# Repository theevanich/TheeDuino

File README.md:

# TheeDuino
My own Arduino board with a RTC!

To open the project with Kicad open atmega328p.pro with Kicad
For schematics see atmega328p.sch
For the PCB see atmega328p.kicad_pcb
Arduino Uno R3 board layout see Arduino_As_Uno.kicad_pcb

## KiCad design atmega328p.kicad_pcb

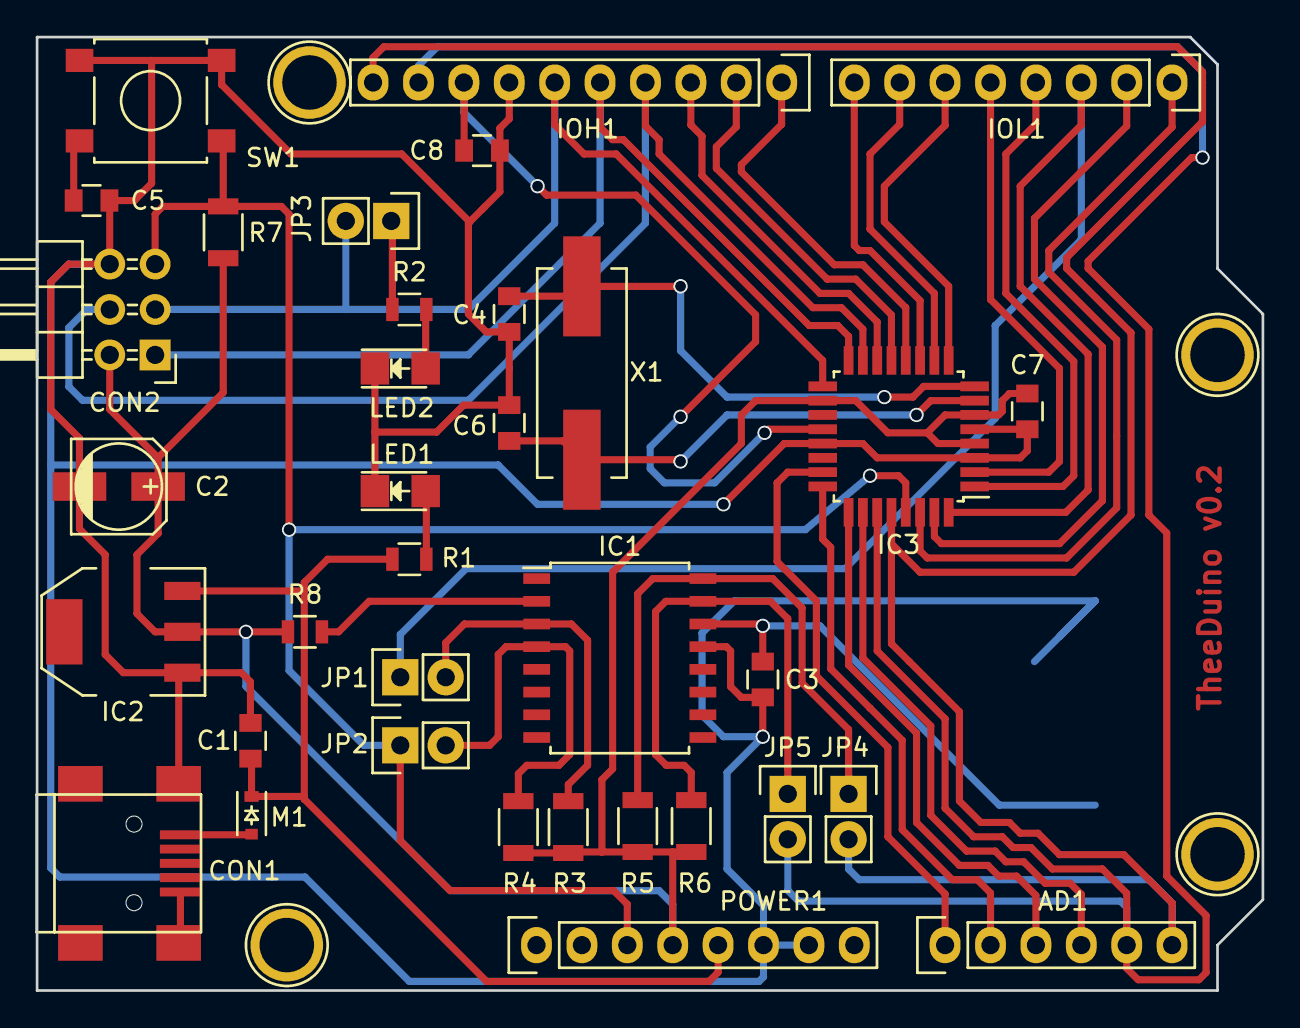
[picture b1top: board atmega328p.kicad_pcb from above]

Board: 2 copper layers, 68.6 x 53.3 mm, 40 parts (1 on the bottom side), 37 nets.

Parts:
AD1: PORT C; Socket_Strip_Arduino_1x06
BATT1: CR2032; 20mmBattHolder
C1, C3, C5, C7, C8: 100nF; C_0805
C2: 10uF; c_elec_5x5.8
C4, C6: 27p; C_0805
CON1: Micro USB; USB_Mini-B
CON2: AVR-ISP-6; Pin_Header_Angled_2x03
IC1: DS3231M_SO16; SOIC-16W_7.5x10.3mm_Pitch1.27mm
IC2: LD1117; SOT-223
IC3: ATMEGA328P-TQFP32; TQFP-32_7x7mm_Pitch0.8mm
IOH1: CONN_01X10; Socket_Strip_Arduino_1x10
IOL1: PORT D; Socket_Strip_Arduino_1x08
JP1, JP2, JP3, JP4, JP5: 1; Pin_Header_Straight_1x02
LED1: POWER; LED_1206
LED2: L; LED_1206
M1: D1; SOD-323
P5, P6, P7, P8: CONN_1; Arduino_1pin
POWER1: POWER; Socket_Strip_Arduino_1x08
R1: 500R; R_0805
R2: 330R; R_0805
R3, R4, R5, R6, R7: 10K; R_1206
R8: 0; R_0805
SW1: RESET; SW_SPST_B3S-1000
X1: 16 MHz; Crystal_HC49-SD_SMD

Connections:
+3V3: C2.1, C7.1, CON2.2, IC2.2, IC3.4, IC3.6, IC3.18, POWER1.4, R3.1, R4.1, R5.2, R6.2, R7.1, R8.1
+5V: C1.1, IC2.3, M1.1, POWER1.5, R1.1
AREF: C8.1, IC3.20, IOH1.8
GND: BATT1.1, C1.2, C2.2, C3.2, C4.2, C5.2, C6.2, C7.2, C8.2, CON1.5, CON1.6, CON2.6, IC1.13, IC2.1, IC3.3, IC3.5, IC3.21, IOH1.7, LED1.1, LED2.1, POWER1.6, POWER1.7, SW1.1
INT0: IC3.32, IOL1.3, JP1.1
unnamed: AD1.1, IC3.23
unnamed: AD1.2, IC3.24
unnamed: AD1.3, IC3.25
unnamed: AD1.4, IC3.26
unnamed: BATT1.2, BATT1.3, C3.1, IC1.14
unnamed: C4.1, IC3.8, X1.1
unnamed: C6.1, IC3.7, X1.2
unnamed: CON1.1, M1.2
unnamed: CON2.1, IC3.16, IOH1.5
unnamed: CON2.4, IC3.15, IOH1.4
unnamed: IC1.2, R8.2
unnamed: IC1.3, JP1.2, R3.2
unnamed: IC1.4, JP2.2, R4.2
unnamed: IC1.15, JP5.1, R6.1
unnamed: IC1.16, JP4.1, R5.1
unnamed: IC3.1, IOL1.4
unnamed: IC3.2, IOL1.5
unnamed: IC3.9, IOL1.6
unnamed: IC3.10, IOL1.7
unnamed: IC3.11, IOL1.8
unnamed: IC3.12, IOH1.1
unnamed: IC3.13, IOH1.2
unnamed: IC3.14, IOH1.3
unnamed: IC3.30, IOL1.1
unnamed: IC3.31, IOL1.2
unnamed: JP3.1, R2.1
unnamed: LED1.2, R1.2
unnamed: LED2.2, R2.2
PB5: CON2.3, IC3.17, IOH1.6, JP3.2
RST: C5.1, CON2.5, IC3.29, JP2.1, POWER1.3, R7.2, SW1.2
SCL: AD1.6, IC3.28, IOH1.10, JP4.2
SDA: AD1.5, IC3.27, IOH1.9, JP5.2

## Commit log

2016-08-15 :circus_tent: Added .gitattributes
2016-08-15 [Add] .gitignore
    to filter out unwanted files in the projects
2016-08-15 Create Readme.md
    Please read me!
2016-08-15 this is needed to be able to see atmega328p in sch
2016-08-15 Update .gitignore
    removed *cache* as it is needed to see some components
2016-08-15 added gerbers and some minor changes
2016-08-22 change batt holder due to wrong footprint
2016-08-23 minor fix and replot gerber
2016-09-28 correct wrong footprint and pinout of atmega328p
2016-09-28 update gerber and drill files
2016-09-28 updated drill files and gerbers
2016-11-08 Updated drill files
2016-12-12 minor changes and overall improvement
